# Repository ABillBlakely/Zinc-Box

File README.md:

# The Zinc Box

### The feature complete RIAA preamp.
#### A Cal Poly AES club project.

## Introduction.

The Zinc Box is an RIAA phono preamp meant to be a simple, high performance preamp for my personal use. The V1.0 was developed solely by myself and was lacking in some of the performance metrics. A new version is being developed within the CPSLO AES club to improve the features and performance of the Zinc Box.

In this repository you will find:
- KiCad contains the project files for schematic capture and PCB creation. In this folder you will also find the Gerber files used for PCB production.
- LTspice folder contains the files used for simulation and testing of project designs.
- Main directory has the current schematic, some reports, and this readme.

## Performance of V1
V1 offered up some pretty decent performance, but has its issues as well. For a more thorough look at performance, check [Performance V1.0.md](Performance V1.0.md).

- Freq Response within +/- 2 dB of ideal across the audio spectrum.
- Channel matching within +/- 0.25 dB.
- THD < 0.05%
- IMD < 0.08%

## Goals
For the second version, subject to change as project is established:
- Match ideal freq response to +/- 0.1dB.
- Lower power supply noise (120 Hz < -90 dB).
- Greatly improved enclosure design, appearance.
- Adjustable input loading.
- THD < 0.005% @ 1 kHz, -3dB output level.
- THD+N < 0.05% @ 1kHz, -3dB output level.
- IMD < 0.05% ITU-R, 13 + 14 kHz 1:1 ratio.

## Updates

#### 2017-3-24 Meeting
We discussed power supply design, and probably tried to cover too many topics in not enough depth. The quick recap:

- The objective of a power supply is to provide stable, constant voltage at the right voltage for the circuit. We know our circuit consists of two op amps so we can figure that we need positive and negative supplies, a total voltage of 20 to 30 volts, and current requirements in the 10's of mA.
- Ripple is the AC noise present on what should be a clean DC supply. V1.0 of the project has problems with power supply noise, so reducing this is a priority.
- An AC voltage must be rectified. The two main types are half-wave and full wave rectification. Full wave wave doubles the ripple frequency while reducing the ripple voltage (both good things) at the expense of requiring 4x the parts count of half wave (or a dedicated IC). 
- An RC filter can reduce ripple, but current will cause a voltage drop across the resistor, and at some point capacitors become physically large and/or expensive, and this limits how effective the filter can be.
- Linear regulators are cheap and easy ways to get a specific voltage output. They come in fixed and variable forms, and usually have around 60 dB (thats a reduction by a factor of 1000) of ripple rejection. 

I am asking that you download the LTSpice folder from up above and install [LTSpice](http://www.linear.com/designtools/software/#LTspice). Ive set up a starting point in 'power supply.asc' from which I would like you to adjust C1, C2, and R1 and try to find a combination that keeps ripple less than 30 uV peak to peak. If you have trouble running the sim, make sure that the two MC78XX files are in the same directory as 'power supply.asc'.

When you have some values that work, go on digikey, mouser or similar and see if you can find the parts available at a reasonable cost. Caps will likely need to be Aluminum electrolytic and should be rated for 50V or higher. 

You may wish to modify the circuit for full wave rectification or make other improvements, any and all improvements are welcome, you can also try simulating a negative regulator using the MC7915. I've added some resources down below specific to power supplies. 

The next official meeting will be the first week of the spring quarter, so there is no rush to get this done during finals week. Questions are welcome in the GroupMe, and let me know if you need to be added to that.

#### Upcoming Meeting 2017-3-10
The next meeting of the Zinc Box preamp project will be Friday, March 10 at 3:00 in the controls lab (20-112).

For this meeting we will be discussing power supply requirements and the basics of power supply design. This meeting will transition out of the workshop style of th first meeting and into having you all doing the hands on design work.

#### 2017-2-24 Meeting
The first meeting held established some of the background of audio testing and measurement.

- I highly recommend you get [ARTA](http://artalabs.hr/), the user manual is pretty good at guiding you through the setup and measurement techniques.
- [Audio Specifications](http://www.rane.com/note145.html) from Rane Audio is a great, succinct, resource for some more detail on the measurements we performed. It also may give you ideas for additional measurements we should make.
- We established some of the goals which are updated in the __Goals__ section above.
- (UPDATE: In room 126.) Next meeting will be Thursday, March 2. We will be performing measurements a little more methodically to produce a new performance report.

## References and Resources
- [LM317]() is a common adjustable regulator, this datasheet has lots of example circuits and aplications worth looking at.
- [MC78XX](http://www.onsemi.com/pub/Collateral/MC7800-D.PDF) is a common fixed positive voltage regulator, the MC79XX are the associated negative voltage regulators.
- [Small, Low Current Power Supplies](http://sound.whsites.net/articles/power-supplies2.htm) from Elliot sound products. This is the second time I've linked to this site, there is lots of good info and example projects here.
- [App note 140, Basic Concepts of Linear Regulator and Switching
Mode Power Supplies](http://cds.linear.com/docs/en/application-note/AN140fa.pdf) from Linear Technology covers some info on when to use linear regulator vs a switching regulator.

- [RIAA Equalization](https://en.wikipedia.org/wiki/RIAA_equalization) from wikipedia for what the RIAA curve is and the history behind the standard.
- [Audio Specifications](http://www.rane.com/note145.html) from Rane Audio for the what and why of audio measurements.
- [ARTA](http://artalabs.hr/) for performing measurements.
- [High-Performance Audio Applications of the LM833](http://www.ti.com/lit/an/snoa586d/snoa586d.pdf) from Texas instruments will be a major reference for design of the filter.
- [Magnetic Phono Pickup Cartridges](http://sound.whsites.net/articles/cartridge-loading.html) from Elliot Sound Products, a discussion on input loading for phono preamps.

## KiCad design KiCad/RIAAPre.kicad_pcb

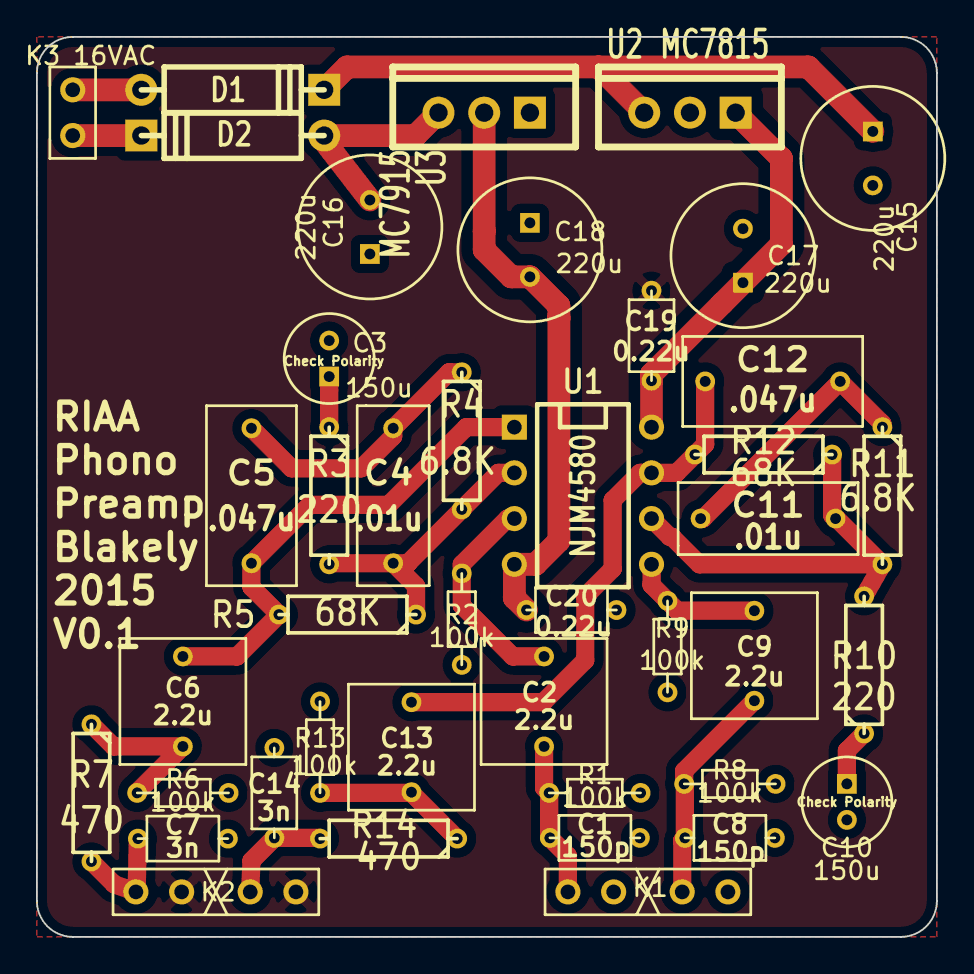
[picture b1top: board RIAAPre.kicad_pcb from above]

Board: 2 copper layers, 50.0 x 50.0 mm, 42 parts (0 on the bottom side), 23 nets.

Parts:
C1, C8: 150p; Cap_4.0x2.5_5.0x0.55
C2, C6, C9, C13: 2.2u; Cap_7.2x7.2_5.0x0.55
C3, C10: 150u; Cap_elec_5.0D_2.0x0.55
C4, C11: .01u; Cap_10x4_7.5x0.5
C5, C12: .047u; Cap_10x5.0_7.5x0.5
C7, C14: 3n; Cap_4.0x2.5_5.0x0.55
C15, C16, C17, C18: 220u; Cap_elec_8.0D_3.5x0.55
C19, C20: 0.22u; Cap_4.0x2.5_5.0x0.55
D1, D2: DIODE; D4
K1, K2: RCA; header4_gap
K3: 16VAC; header2
R1, R2, R6, R8, R9, R13: 100k; R_3.0x1.5_5.0x0.55
R3, R10: 220; R_6.5x2.0_7.5x0.55
R4, R11: 6.8K; R_6.5x2.0_7.5x0.55
R5, R12: 68K; R_6.5x2.0_7.5x0.55
R7, R14: 470; R_6.5x2.0_7.5x0.55
U1: NJM4580; DIP-8__300
U2: MC7815; TO220_VERT
U3: MC7915; TO220_VERT

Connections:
/+15V: C17.1, C19.1, U1.8, U2.3
/-15V: C18.2, C20.2, U1.4, U3.2
GND: C1.2, C3.2, C7.2, C8.2, C10.2, C14.2, C15.2, C16.1, C17.2, C18.1, C19.2, C20.1, K1.2, K1.4, K2.2, K2.4, R1.2, R2.2, R6.2, R8.2, R9.2, R13.2, U2.2
unnamed: C1.1, C2.1, K1.1, R1.1
unnamed: C3.1, R3.1
unnamed: C10.1, R10.1
unnamed: C6.2, R6.1, R7.1
unnamed: C12.2, C13.1, R12.2, U1.7
unnamed: C4.2, C5.1, R4.1
unnamed: C7.1, K2.1, R7.2
unnamed: C5.2, C6.1, R5.2, U1.1
unnamed: C4.1, R3.2, R4.2, R5.1, U1.2
unnamed: C2.2, R2.1, U1.3
unnamed: C16.2, D2.1, U3.1
unnamed: C15.1, D1.2, U2.1
unnamed: D2.2, K3.2
unnamed: C8.1, C9.1, K1.3, R8.1
unnamed: C11.2, C12.1, R11.1
unnamed: C11.1, R10.2, R11.2, R12.1, U1.6
unnamed: C13.2, R13.1, R14.1
unnamed: D1.1, K3.1
unnamed: C14.1, K2.3, R14.2
unnamed: C9.2, R9.1, U1.5

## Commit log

2016-03-05 Initial Commit. V1.0 of the Riaa Preamp.
2016-03-05 Add initial readme file.
2016-03-06 Add performance file, image links will likely need to be fixed later
2016-03-06 Directory cleanup and ignore additions.
2016-03-06 Added performance folder with figures and data
2016-03-06 Update .gitignore.
2016-03-06 Fix issue with IMD test image not displaying
2016-03-06 Fix filename problem that prevented images from showing.
2016-03-06 Add v1.0 schematic in pdf
2016-03-06 Update readme, change .gitignore pdf rules.
2016-03-07 Fix issue traker link.
2016-04-12 Fixed and it's/its typo.
2016-04-19 Fix a few typos in performance report.
2016-04-19 Fix table in performance report.
2016-04-20 Project name change.
2017-02-23 Add cartridge loading simulation
2017-02-23 Add script for generation of freq response graphs.
2017-02-23 Update simulation command and data.
2017-02-23 Cover all google document types.
2017-02-23 Clean up imports.
2017-02-26 Exclude autosaves, Remove some obsolete exclusions.
2017-02-26 Restructure to provide information to the group.
2017-03-02 Add room for meeting.
2017-03-03 Add image captures of new performance measurements.
2017-03-03 Remove old response files.
2017-03-06 Clean and fix so script works with current data.
2017-03-06 Add current measurment data and figures, update spice sim to match.
2017-03-06 Create an ideal transfer curve circuit and symbol in LTSpice.
2017-03-06 Add new measurement data to project.
2017-03-06 Add ideal response to simulation for comparison, Change C7 to match schematic value.
2017-03-06 Remove spaces from filenames.
2017-03-06 Update to represent the new performance measurements.
2017-03-06 Fix link for noise figure.
2017-03-08 Add details of 2017-3-10 upcoming meeting.
2017-03-10 Update power supply design with models of MC78XX.
2017-03-12 Include Spice Models of MC78XX and MC79XX regulators.
2017-03-12 Change image export filenames.
2017-03-14 Fix the power sim so it uses the correct library.
2017-03-14 Include details of 3-24 meeting and current tasks.
